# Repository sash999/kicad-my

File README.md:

# kicad-my
папка с кикадовскими проектами

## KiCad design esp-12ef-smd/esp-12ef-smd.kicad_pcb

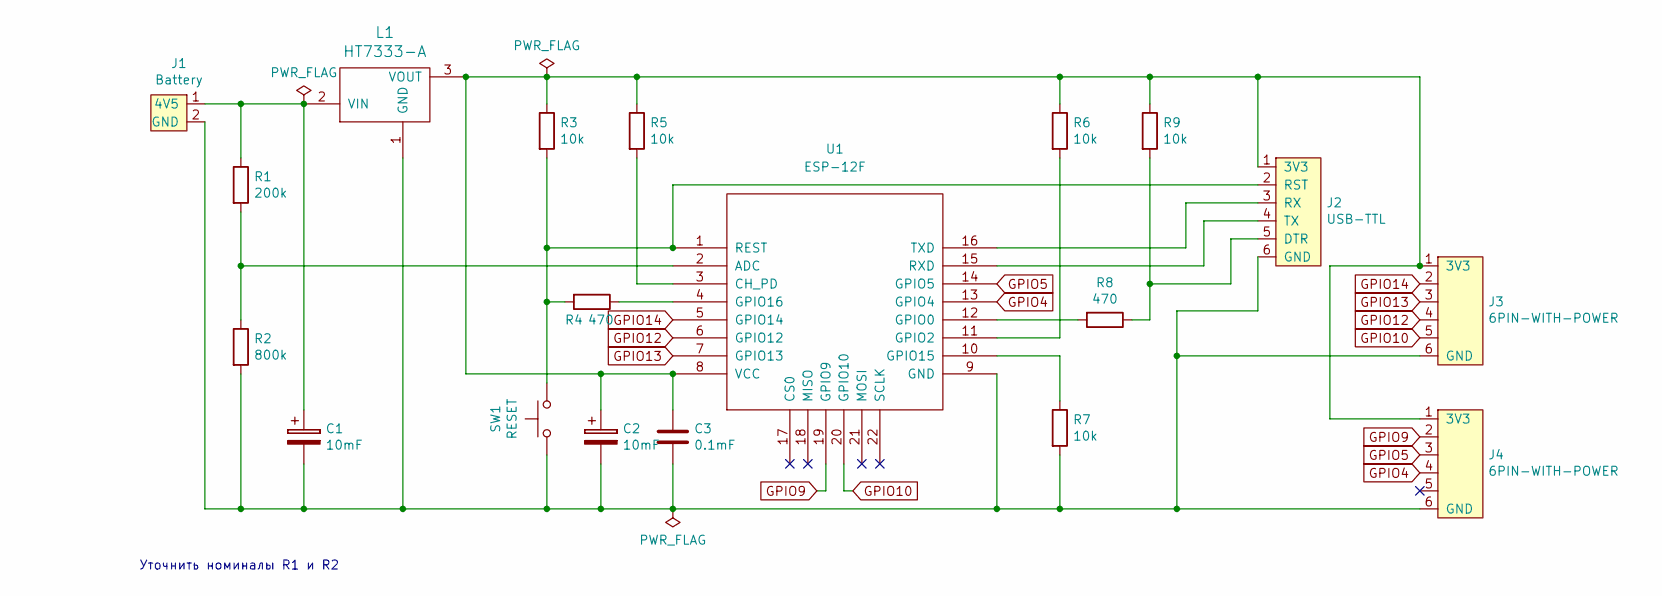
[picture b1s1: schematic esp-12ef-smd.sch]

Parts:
C1, C2: 10mF; CP_Elec_5x3
C3: 0.1mF; C_0805_2012Metric_Pad1.15x1.40mm_HandSolder
J1: Battery; PinHeader_1x02_P2.54mm_Vertical
J2: USB-TTL; PinSocket_1x06_P2.54mm_Vertical
J3, J4: 6PIN-WITH-POWER; PinSocket_1x06_P2.54mm_Vertical
L1: HT7333-A; ht7333-a
R1: 200k; R_0805_2012Metric_Pad1.15x1.40mm_HandSolder
R2: 800k; R_0805_2012Metric_Pad1.15x1.40mm_HandSolder
R3, R5, R6, R7, R9: 10k; R_0805_2012Metric_Pad1.15x1.40mm_HandSolder
R4, R8: 470; R_0805_2012Metric_Pad1.15x1.40mm_HandSolder
SW1: RESET; SW_PUSH_6mm
U1: ESP-12F; ESP-12E

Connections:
GPIO4: J4.4, U1.13 (GPIO4)
GPIO5: J4.3, U1.14 (GPIO5)
GPIO9: J4.2, U1.19 (GPIO9)
GPIO10: J3.5, U1.20 (GPIO10)
GPIO12: J3.4, U1.6 (GPIO12)
GPIO13: J3.3, U1.7 (GPIO13)
GPIO14: J3.2, U1.5 (GPIO14)
unnamed: C1.1, J1.1 (4V5), L1.2 (VIN), R1.1
unnamed: C1.2, C2.2, C3.2, J1.2 (GND), J2.6 (GND), J3.6 (GND), J4.6 (GND), L1.1 (GND), R2.2, R7.2, SW1.1, U1.9 (GND)
unnamed: C2.1, C3.1, J2.1 (3V3), J3.1 (3V3), J4.1 (3V3), L1.3 (VOUT), R3.1, R5.1, R6.1, R9.1, U1.8 (VCC)
unnamed: J2.2 (RST), R3.2, R4.2, SW1.2, U1.1 (REST)
unnamed: J2.3 (RX), U1.16 (TXD)
unnamed: J2.4 (TX), U1.15 (RXD)
unnamed: J2.5 (DTR), R8.1, R9.2
unnamed: R1.2, R2.1, U1.2 (ADC)
unnamed: R4.1, U1.4 (GPIO16)
unnamed: R5.2, U1.3 (CH_PD)
unnamed: R6.2, U1.11 (GPIO2)
unnamed: R7.1, U1.10 (GPIO15)
unnamed: R8.2, U1.12 (GPIO0)

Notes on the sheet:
Уточнить номиналы R1 и R2

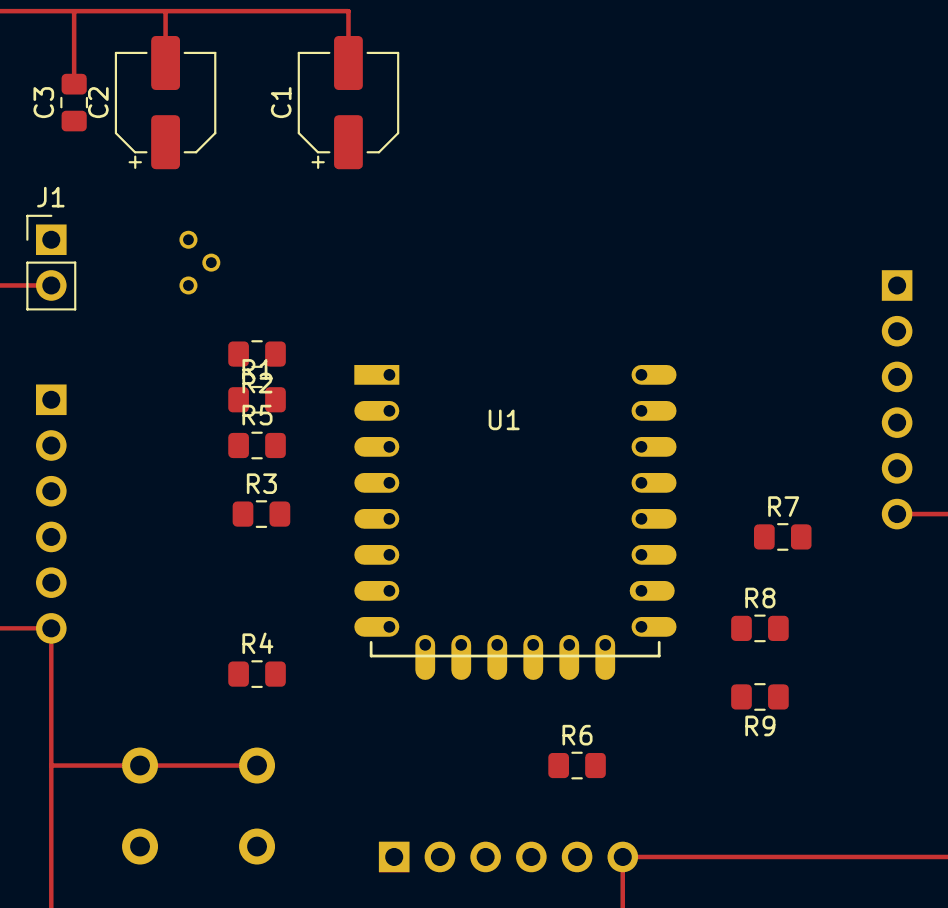
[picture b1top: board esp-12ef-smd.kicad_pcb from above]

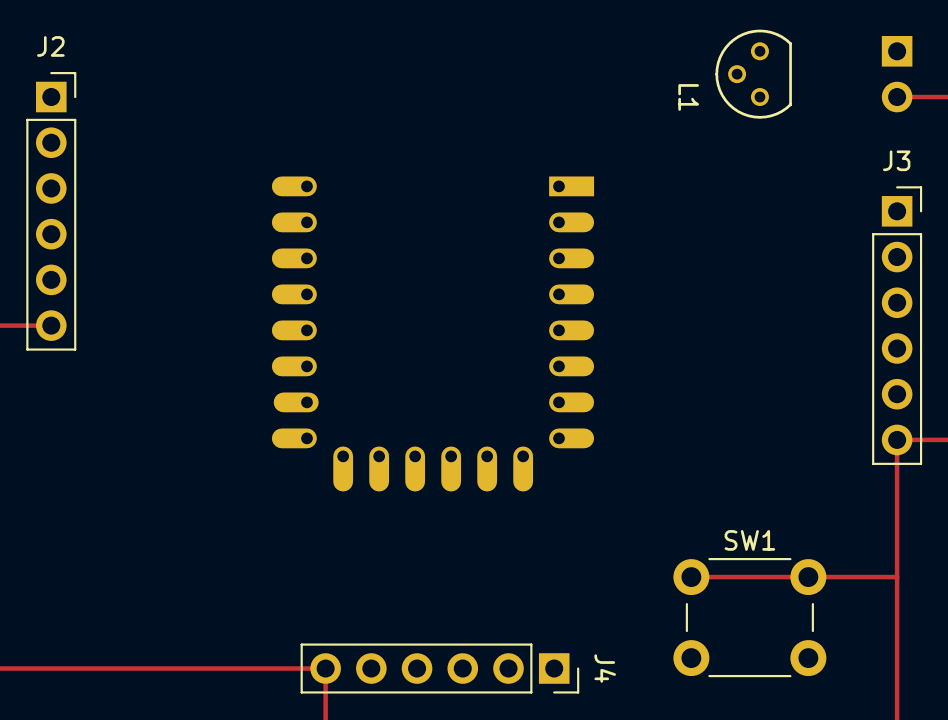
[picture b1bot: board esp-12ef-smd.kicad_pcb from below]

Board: 2 copper layers, 19 parts (5 on the bottom side), 20 nets.

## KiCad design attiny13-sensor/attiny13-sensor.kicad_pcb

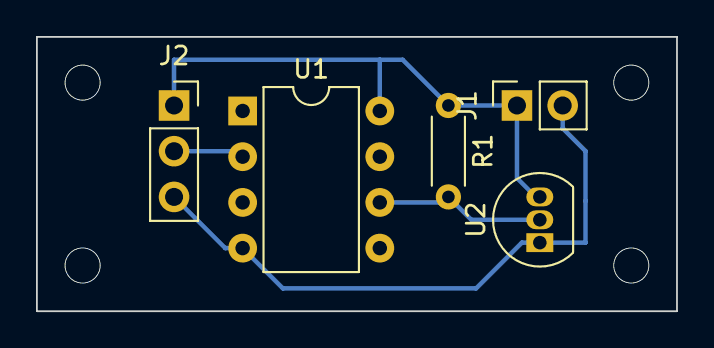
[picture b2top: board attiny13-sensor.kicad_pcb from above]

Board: 2 copper layers, 35.6 x 15.2 mm, 5 parts (0 on the bottom side), 4 nets.

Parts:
J1: Battery; PinSocket_1x02_P2.54mm_Vertical
J2: RX433_CONNECTOR; PinSocket_1x03_P2.54mm_Vertical
R1: 4k7; R_Axial_DIN0204_L3.6mm_D1.6mm_P5.08mm_Horizontal
U1: ATtiny13A-PU; DIP-8_W7.62mm
U2: DS18B20; TO-92_Inline

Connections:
unnamed: J1.1, J2.1, R1.1, U1.8, U2.3
unnamed: J1.2, J2.3, U1.4, U2.1
unnamed: J2.2, U1.2
unnamed: R1.2, U1.6, U2.2

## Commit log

2019-02-07 pcb done
2019-02-11 уменьшен размер платы
2019-02-12 пытаемся развести smd в один слой
2019-02-12 little fixes
2019-04-11 minor changes
2019-04-12 README update
2019-04-12 test
2019-04-22 новый проект - attiny13-sensor
2019-04-22 modified attiny project
2019-04-24 добавлены либы и пробный проект для lolin nodemcu v3
2019-04-25 нарисована базовая схема
2019-06-06 added nodemcu pinout scheme
